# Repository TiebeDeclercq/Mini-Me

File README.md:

# Mini-Me

An animatronic robot that naturally mimics human movements with multiple control interfaces (UDP & Bottango)

## Hardware Overview

The system uses a dual-microcontroller architecture:
- **STM32G030C8T:** Hardware control and servo management
- **ESP32-WROOM-32E-N8:** WiFi communication and external interfaces
- **19 servo motors** controlled via 2x PCA9685 PWM drivers
- **Custom PCBs** for main control and servo distribution
- **12V power supply** with buck converter and current monitoring

## Assembly Instructions

**3D Printed Parts**
The mechanical design consists of 22 different parts, all designed in Fusion 360 for the Bambu Lab P1S printer. Print all STL files from the `/Printfiles/` directory.

**Magnet Integration**
During printing, pause the G-code at specified layers to insert magnets into the head, arms, and legs. This allows easy attachment of accessories and face variations.

**PCB Assembly**
1. Order PCBs using Gerber files in `/Pcb's/`
2. Solder components according to the provided BOMs
3. Main board includes ESP32, STM32, power management, and interfaces
4. Servo boards use JST connectors for secure servo connections

**Final Assembly**
1. Install PCBs in the base/foot assembly
2. Connect servo boards via ribbon cables

3. Mount OLED display and rotary encoder in base

4. Assemble skeleton parts with integrated magnets
5. Connect all servos to appropriate servo board positions

## Software

**Firmware**
- **ESP32:** Programmed with PlatformIO (C++)
- **STM32:** Programmed with STM32CubeIDE

**Control Applications**
- **Mobile App (Flutter):** Smartphone-based control interface via UDP
- **Bottango Integration:** Professional animation software compatibility

**Network Control**
The robot accepts UDP commands in JSON format:
```json
{"servo": 1, "angle": 90}
{"servos": [{"id": 1, "angle": 90}, {"id": 2, "angle": 45}]}
```

## Getting Started

1. **3D Print** all parts from `/Printfiles/`
2. **Order and assemble** PCBs using provided files and BOMs
3. **Flash firmware** from `/Firmware/Mini-Me-DevBoard/` and `/Firmware/MINI-ME-ESP32/`
4. **Install control software** of choice from `/Software/`
5. **Connect to WiFi** and start controlling via UDP or applications

**Project Report:** [Complete documentation available](docs/Mini-Me-Report.pdf)

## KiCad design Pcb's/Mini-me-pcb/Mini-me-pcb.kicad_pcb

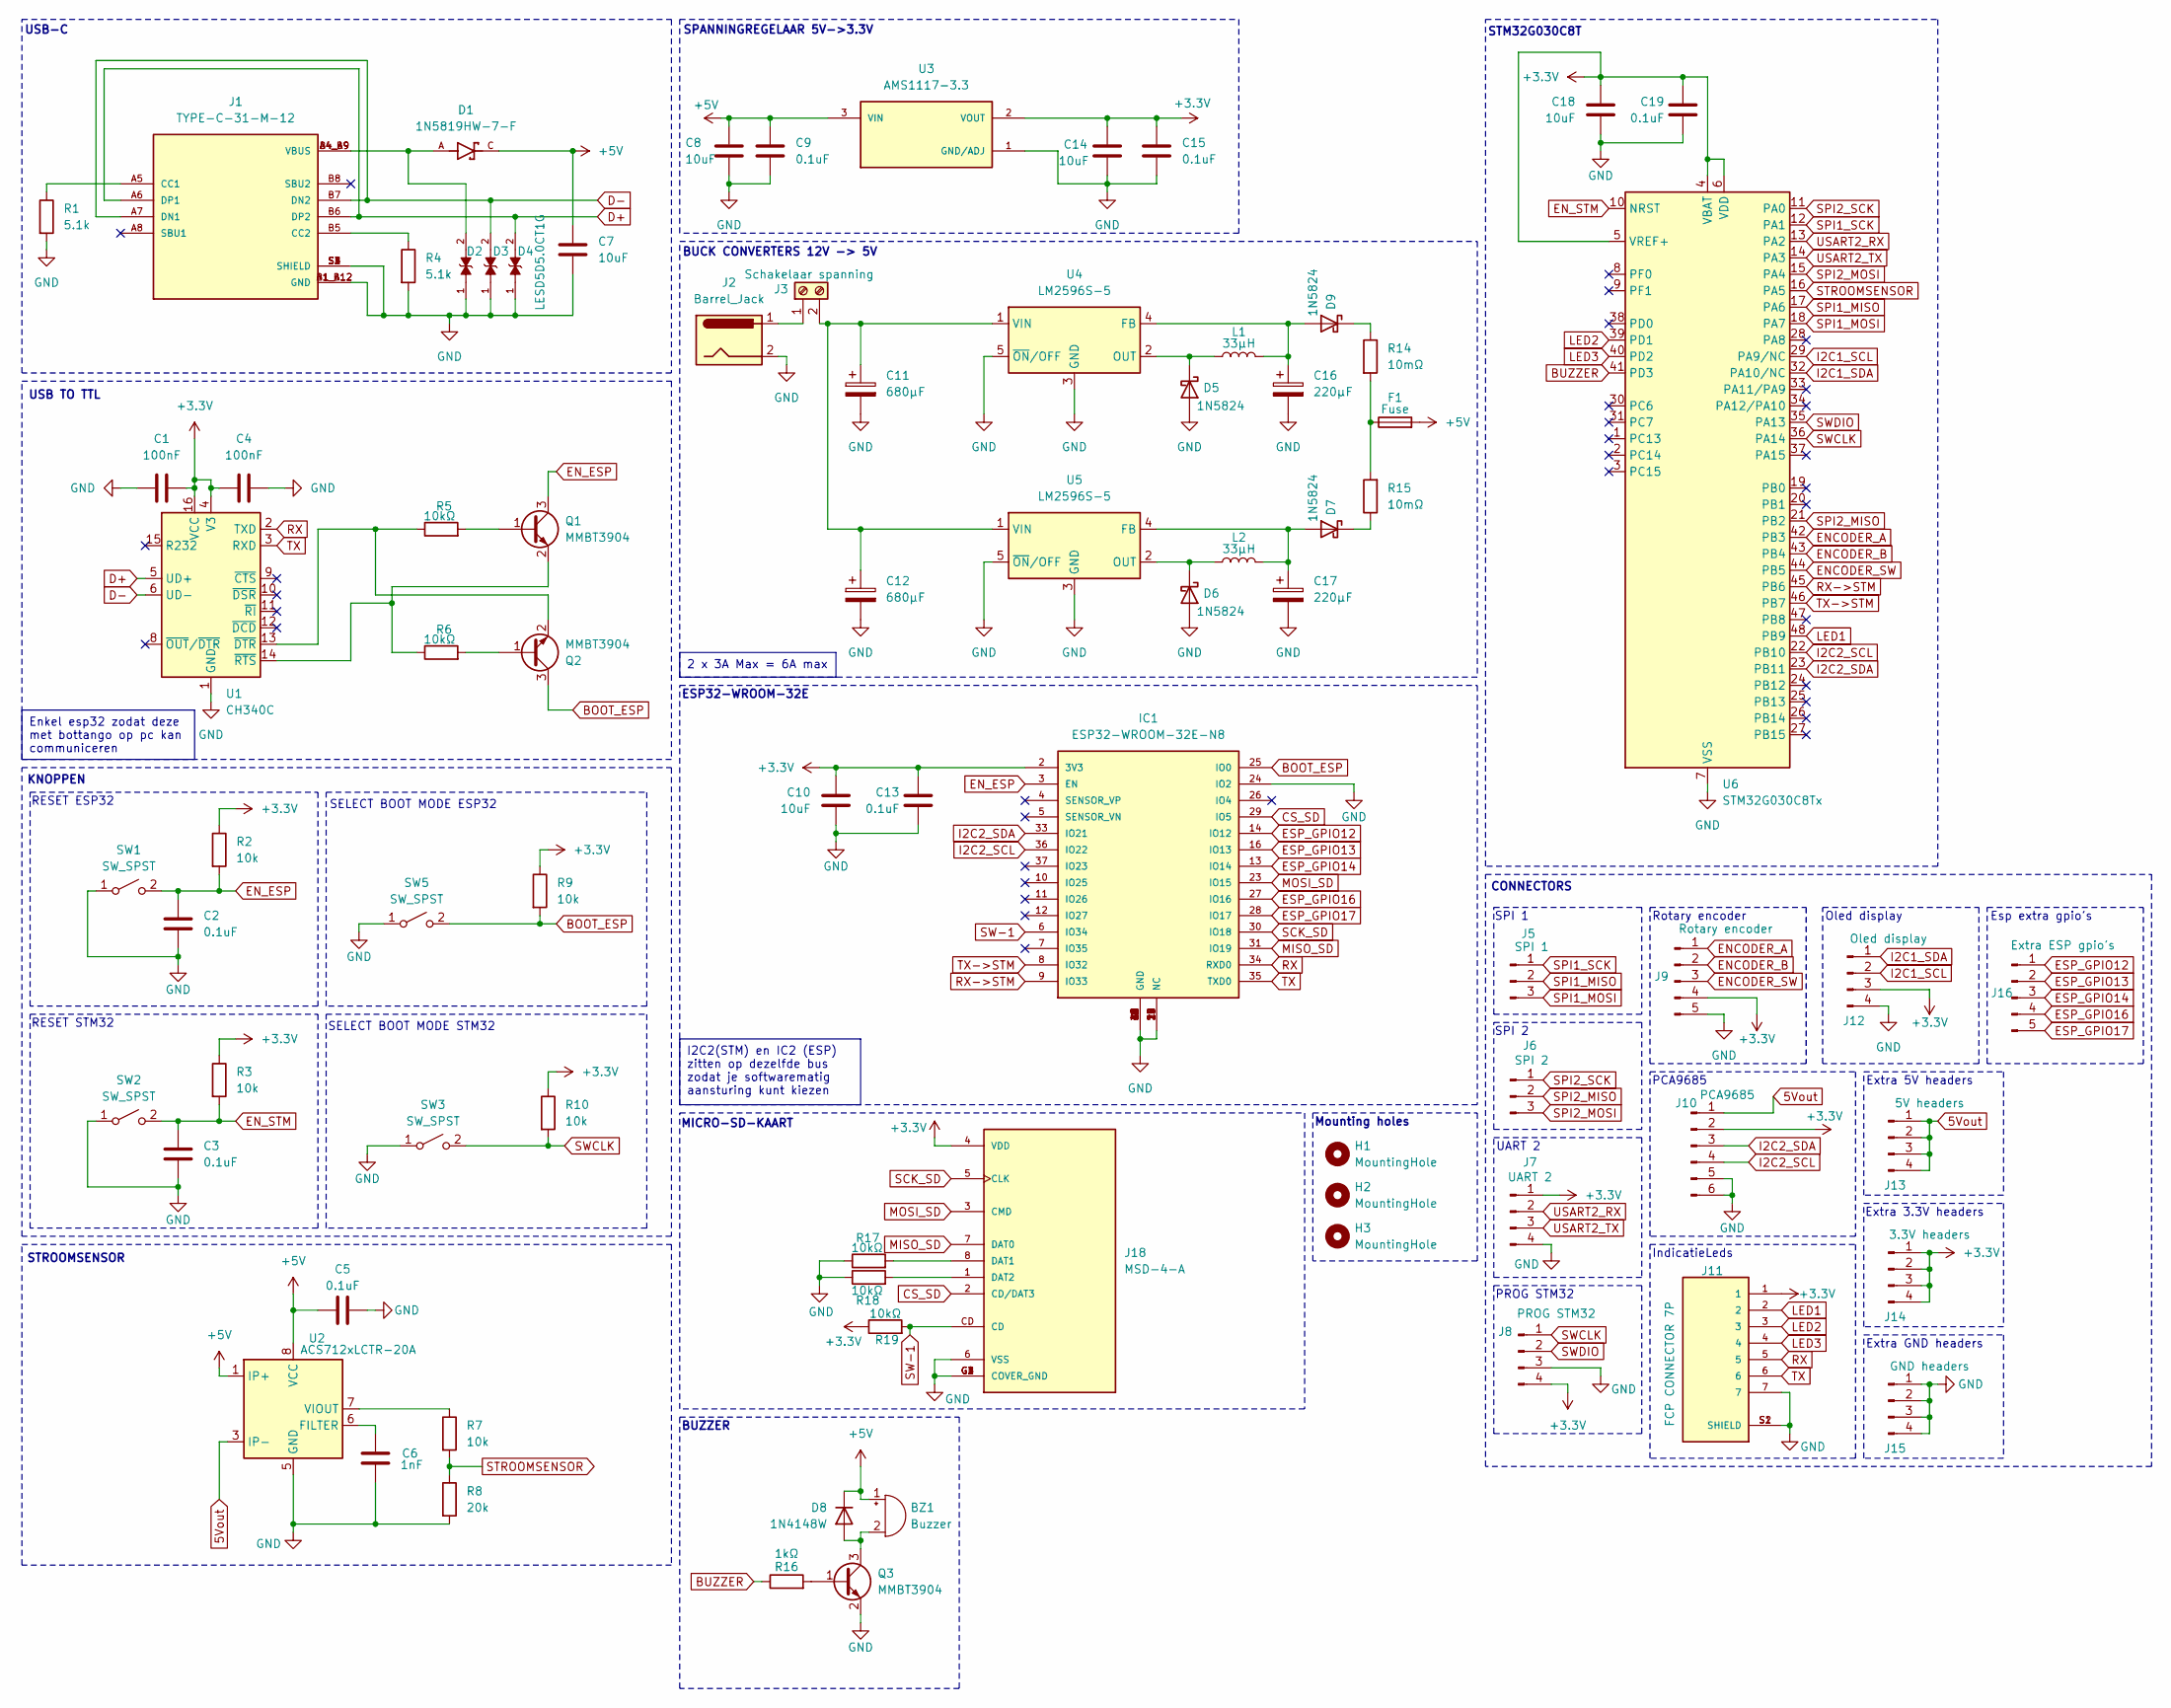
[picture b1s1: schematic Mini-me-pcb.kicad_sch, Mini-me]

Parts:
BZ1: Buzzer; MagneticBuzzer_PUI_AT-0927-TT-6-R
C1, C4: 100nF; C_0805_2012Metric_Pad1.18x1.45mm_HandSolder
C2, C3, C5, C9, C13, C15, C19: 0.1uF; C_0805_2012Metric_Pad1.18x1.45mm_HandSolder
C6: 1nF; C_0805_2012Metric_Pad1.18x1.45mm_HandSolder
C7, C8, C10, C14, C18: 10uF; C_0805_2012Metric_Pad1.18x1.45mm_HandSolder
C11, C12: 680µF; CP_Elec_10x10
C16, C17: 220µF; CP_Elec_6.3x7.7
D1: 1N5819HW-7-F; SOD3715X145N; PARTREV 18-2
D2, D3, D4: LESD5D5.0CT1G; TVS_LESD5D5.0CT1G; PARTREV O
D5, D6, D7, D9: 1N5824; D_SMA
D8: 1N4148W; D_SOD-123
F1: Fuse; Fuse_1206_3216Metric
H1, H2, H3: MountingHole; MountingHole_3.2mm_M3
IC1: ESP32-WROOM-32E-N8; ESP32WROOM32EN8; MOUSER_PART_NUMBER 356-ESP32WRM32E164PH
J1: TYPE-C-31-M-12; HRO_TYPE-C-31-M-12; PARTREV 2020.12.08
J2: Barrel_Jack; BarrelJack_GCT_DCJ200-10-A_Horizontal
J3: Schakelaar spanning; TerminalBlock_Phoenix_MKDS-1,5-2-5.08_1x02_P5.08mm_Horizont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
J5: SPI 1; PinHeader_1x03_P2.54mm_Vertical
J6: SPI 2; PinHeader_1x03_P2.54mm_Vertical
J7: UART 2; PinHeader_1x04_P2.54mm_Vertical
J8: PROG STM32; PinHeader_1x04_P2.54mm_Vertical
J9: Rotary encoder; JST_PH_B5B-PH-K_1x05_P2.00mm_Vertical
J10: PCA9685; JST_PH_B6B-PH-K_1x06_P2.00mm_Vertical
J11: FCP CONNECTOR 7P; FCP7P; PARTREV A4
J12: Oled display; JST_PH_B4B-PH-K_1x04_P2.00mm_Vertical
J13: 5V headers; PinHeader_1x04_P2.54mm_Vertical
J14: 3.3V headers; PinHeader_1x04_P2.54mm_Vertical
J15: GND headers; PinHeader_1x04_P2.54mm_Vertical
J16: Extra ESP gpio's; PinHeader_1x05_P2.54mm_Vertical
J18: MSD-4-A; CUI_MSD-4-A; PARTREV 1.0
L1, L2: 33µH; L_SXN_SMDRI125
Q1, Q2, Q3: MMBT3904; SOT-23
R1, R4: 5.1k; R_0805_2012Metric_Pad1.20x1.40mm_HandSolder
R2, R3, R7, R9, R10: 10k; R_0805_2012Metric_Pad1.20x1.40mm_HandSolder
R5, R6, R17, R18, R19: 10kΩ; R_0805_2012Metric_Pad1.20x1.40mm_HandSolder
R8: 20k; R_0805_2012Metric_Pad1.20x1.40mm_HandSolder
R14, R15: 10mΩ; R_2512_6332Metric
R16: 1kΩ; R_0805_2012Metric_Pad1.20x1.40mm_HandSolder
SW1, SW2, SW3, SW5: SW_SPST; SW_SPST_PTS645
U1: CH340C; SOIC-16_3.9x9.9mm_P1.27mm
U2: ACS712xLCTR-20A; SOIC-8_3.9x4.9mm_P1.27mm
U3: AMS1117-3.3; SOT-223; PARTREV N/A
U4, U5: LM2596S-5; TO-263-5_TabPin3
U6: STM32G030C8Tx; LQFP-48_7x7mm_P0.5mm

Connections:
5Vout: J10.1, J13.1, J13.2, J13.3, J13.4, U2.3 (IP-), U2.4 (IP-)
+3.3V: C1.2, C4.1, C10.1, C13.1, C14.1, C15.1, C18.1, C19.1, IC1.2 (3V3), J7.1, J8.4, J9.4, J10.2, J11.1, J12.3, J14.1, J14.2, J14.3, J14.4, J18.4 (VDD), R2.1, R3.1, R9.1, R10.1, R19.1, U1.4 (V3), U1.16 (VCC), U3.2 (VOUT), U6.4 (VBAT), U6.5 (VREF+), U6.6 (VDD)
+5V: BZ1.1 (-), C5.1, C7.1, C8.1, C9.1, D1.C, D8.1 (K), F1.2, U2.1 (IP+), U2.2 (IP+), U2.8 (VCC), U3.3 (VIN)
BOOT_ESP: IC1.25 (IO0), Q2.3 (C), R9.2, SW5.2 (B)
BUZZER: R16.1, U6.41 (PD3)
CS_SD: IC1.29 (IO5), J18.2 (CD/DAT3)
D+: D4.2, J1.A6 (DP1), J1.B6 (DP2), U1.5 (UD+)
D-: D3.2, J1.A7 (DN1), J1.B7 (DN2), U1.6 (UD-)
ENCODER_A: J9.1, U6.42 (PB3)
ENCODER_B: J9.2, U6.43 (PB4)
ENCODER_SW: J9.3, U6.44 (PB5)
EN_ESP: C2.1, IC1.3 (EN), Q1.3 (C), R2.2, SW1.2 (B)
EN_STM: C3.1, R3.2, SW2.2 (B), U6.10 (NRST)
ESP_GPIO12: IC1.14 (IO12), J16.1
ESP_GPIO13: IC1.16 (IO13), J16.2
ESP_GPIO14: IC1.13 (IO14), J16.3
ESP_GPIO16: IC1.27 (IO16), J16.4
ESP_GPIO17: IC1.28 (IO17), J16.5
GND: C1.1, C2.2, C3.2, C4.2, C5.2, C6.2, C7.2, C8.2, C9.2, C10.2, C11.2, C12.2, C13.2, C14.2, C15.2, C16.2, C17.2, C18.2, C19.2, D2.1, D3.1, D4.1, D5.2 (A), D6.2 (A), IC1.1 (GND), IC1.15 (GND), IC1.17 (NC), IC1.18 (NC), IC1.19 (NC), IC1.20 (NC), IC1.21 (NC), IC1.22 (NC), IC1.24 (IO2), IC1.32 (NC), IC1.38 (GND), IC1.39 (GND), IC1.40 (GND), IC1.41 (GND), IC1.42 (GND), IC1.43 (GND), IC1.44 (GND), IC1.45 (GND), IC1.46 (GND), IC1.47 (GND), J1.A1_B12 (GND), J1.B1_A12 (GND), J1.S1 (SHIELD), J1.S2 (SHIELD), J1.S3 (SHIELD), J1.S4 (SHIELD), J2.2, J7.4, J8.3, J9.5, J10.5, J10.6, J11.7, J11.S1 (SHIELD), J11.S2 (SHIELD), J12.4, J15.1, J15.2, J15.3, J15.4, J18.6 (VSS), J18.G1 (COVER_GND), J18.G2 (COVER_GND), J18.G3 (COVER_GND), J18.G4 (COVER_GND), Q3.2 (E), R1.2, R4.2, R8.2, R17.1, R18.1, SW1.1 (A), SW2.1 (A), SW3.1 (A), SW5.1 (A), U1.1 (GND), U2.5 (GND), U3.1 (GND/ADJ), U4.3 (GND), U4.5 (~ON/OFF), U5.3 (GND), U5.5 (~ON/OFF), U6.7 (VSS)
I2C1_SCL: J12.2, U6.29 (PA9/NC)
I2C1_SDA: J12.1, U6.32 (PA10/NC)
I2C2_SCL: IC1.36 (IO22), J10.4, U6.22 (PB10)
I2C2_SDA: IC1.33 (IO21), J10.3, U6.23 (PB11)
LED1: J11.2, U6.48 (PB9)
LED2: J11.3, U6.39 (PD1)
LED3: J11.4, U6.40 (PD2)
MISO_SD: IC1.31 (IO19), J18.7 (DAT0)
MOSI_SD: IC1.23 (IO15), J18.3 (CMD)
unnamed: BZ1.2 (+), D8.2 (A), Q3.3 (C)
unnamed: D1.A, D2.2, J1.A4_B9 (VBUS), J1.B4_A9 (VBUS)
unnamed: D5.1 (K), L1.1, U4.2 (OUT)
unnamed: D6.1 (K), L2.1, U5.2 (OUT)
unnamed: C17.1, D7.2 (A), L2.2, U5.4 (FB)
unnamed: D7.1 (K), R15.1
unnamed: C16.1, D9.2 (A), L1.2, U4.4 (FB)
unnamed: D9.1 (K), R14.1
unnamed: F1.1, R14.2, R15.2
unnamed: J1.A5 (CC1), R1.1
unnamed: J1.B5 (CC2), R4.1
unnamed: J2.1, J3.1
unnamed: C11.1, C12.1, J3.2, U4.1 (VIN), U5.1 (VIN)
unnamed: J18.8 (DAT1), R17.2
unnamed: J18.1 (DAT2), R18.2
unnamed: Q1.1 (B), R5.2
unnamed: Q1.2 (E), R6.1, U1.14 (~RTS)
unnamed: Q2.1 (B), R6.2
unnamed: Q2.2 (E), R5.1, U1.13 (~DTR)
unnamed: Q3.1 (B), R16.2
unnamed: C6.1, U2.6 (FILTER)
unnamed: R7.1, U2.7 (VIOUT)
RX: IC1.34 (RXD0), J11.5, U1.2 (TXD)
RX->STM: IC1.9 (IO33), U6.45 (PB6)
SCK_SD: IC1.30 (IO18), J18.5 (CLK)
SPI1_MISO: J5.2, U6.17 (PA6)
SPI1_MOSI: J5.3, U6.18 (PA7)
SPI1_SCK: J5.1, U6.12 (PA1)
SPI2_MISO: J6.2, U6.21 (PB2)
SPI2_MOSI: J6.3, U6.15 (PA4)
SPI2_SCK: J6.1, U6.11 (PA0)
STROOMSENSOR: R7.2, R8.1, U6.16 (PA5)
SW-1: IC1.6 (IO34), J18.CD, R19.2
SWCLK: J8.1, R10.2, SW3.2 (B), U6.36 (PA14)
SWDIO: J8.2, U6.35 (PA13)
TX: IC1.35 (TXD0), J11.6, U1.3 (RXD)
TX->STM: IC1.8 (IO32), U6.46 (PB7)
USART2_RX: J7.2, U6.13 (PA2)
USART2_TX: J7.3, U6.14 (PA3)

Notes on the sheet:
I2C2(STM) en IC2 (ESP) zitten op dezelfde bus zodat je softwarematig aansturing kunt kiezen
Enkel esp32 zodat deze met bottango op pc kan communiceren
2 x 3A Max = 6A max
STM32G030C8T
SELECT BOOT MODE ESP32
SPI 2
BUZZER
Extra 3.3V headers
Oled display
Mounting holes
STROOMSENSOR
Extra GND headers
MICRO-SD-KAART
USB-C
Esp extra gpio's
SPANNINGREGELAAR 5V->3.3V
Rotary encoder
IndicatieLeds
UART 2
Extra 5V headers
SELECT BOOT MODE STM32
KNOPPEN
SPI 1
PCA9685
RESET STM32
RESET ESP32
CONNECTORS
USB TO TTL
BUCK CONVERTERS 12V -> 5V
ESP32-WROOM-32E
PROG STM32

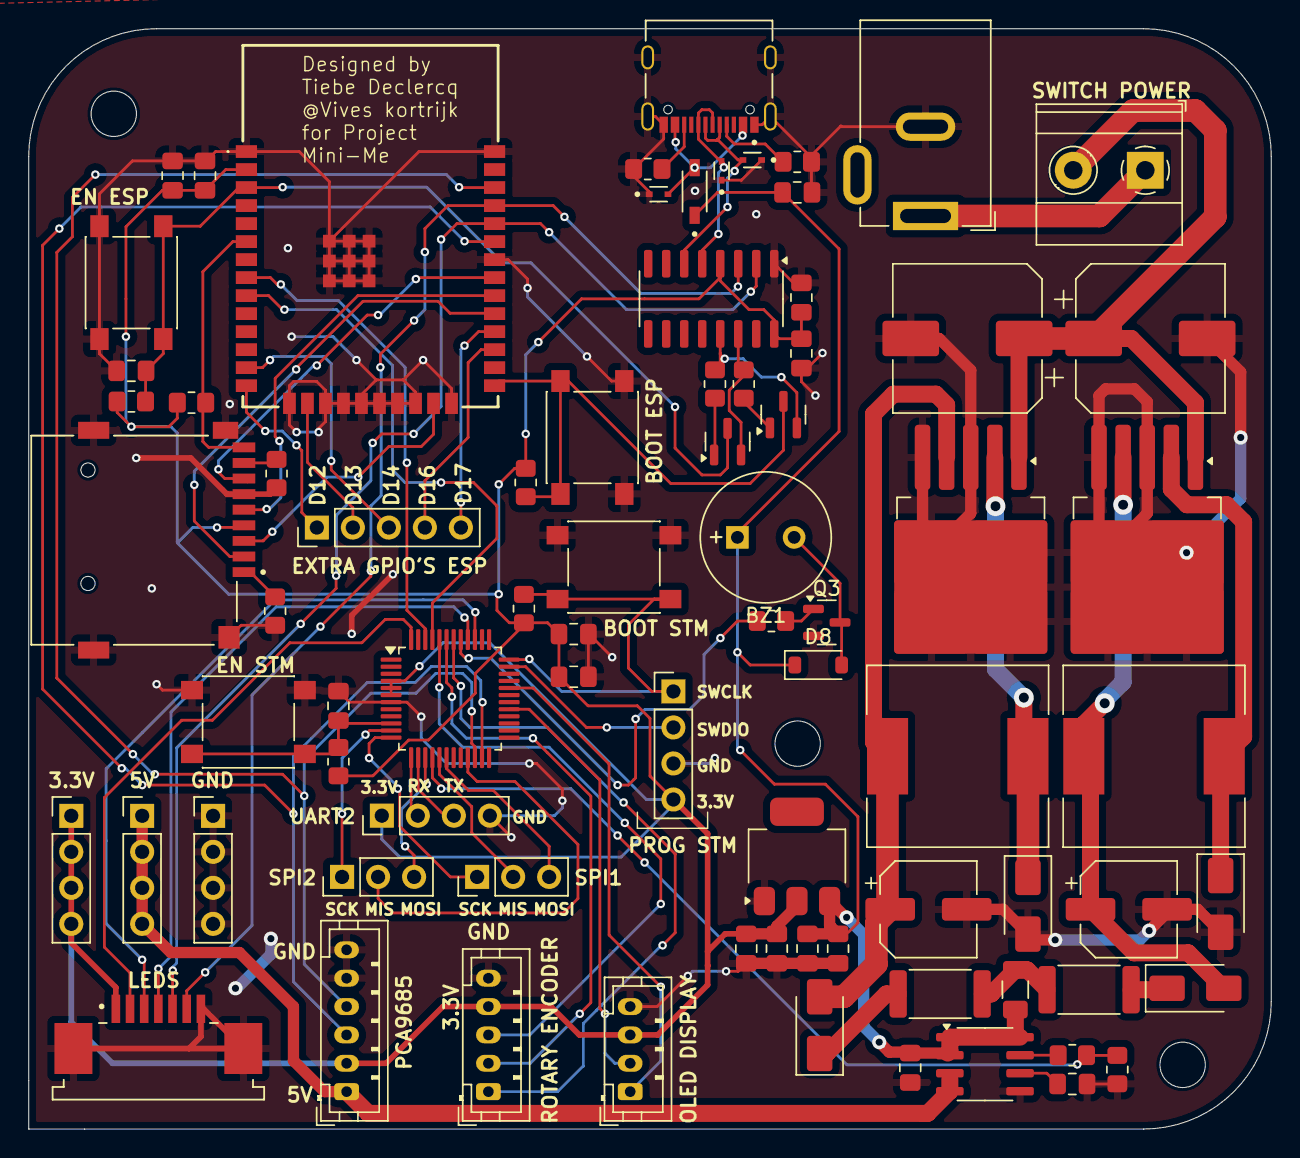
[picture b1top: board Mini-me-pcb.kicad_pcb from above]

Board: 2 copper layers, 87.6 x 77.6 mm, 81 parts (0 on the bottom side), 67 nets.

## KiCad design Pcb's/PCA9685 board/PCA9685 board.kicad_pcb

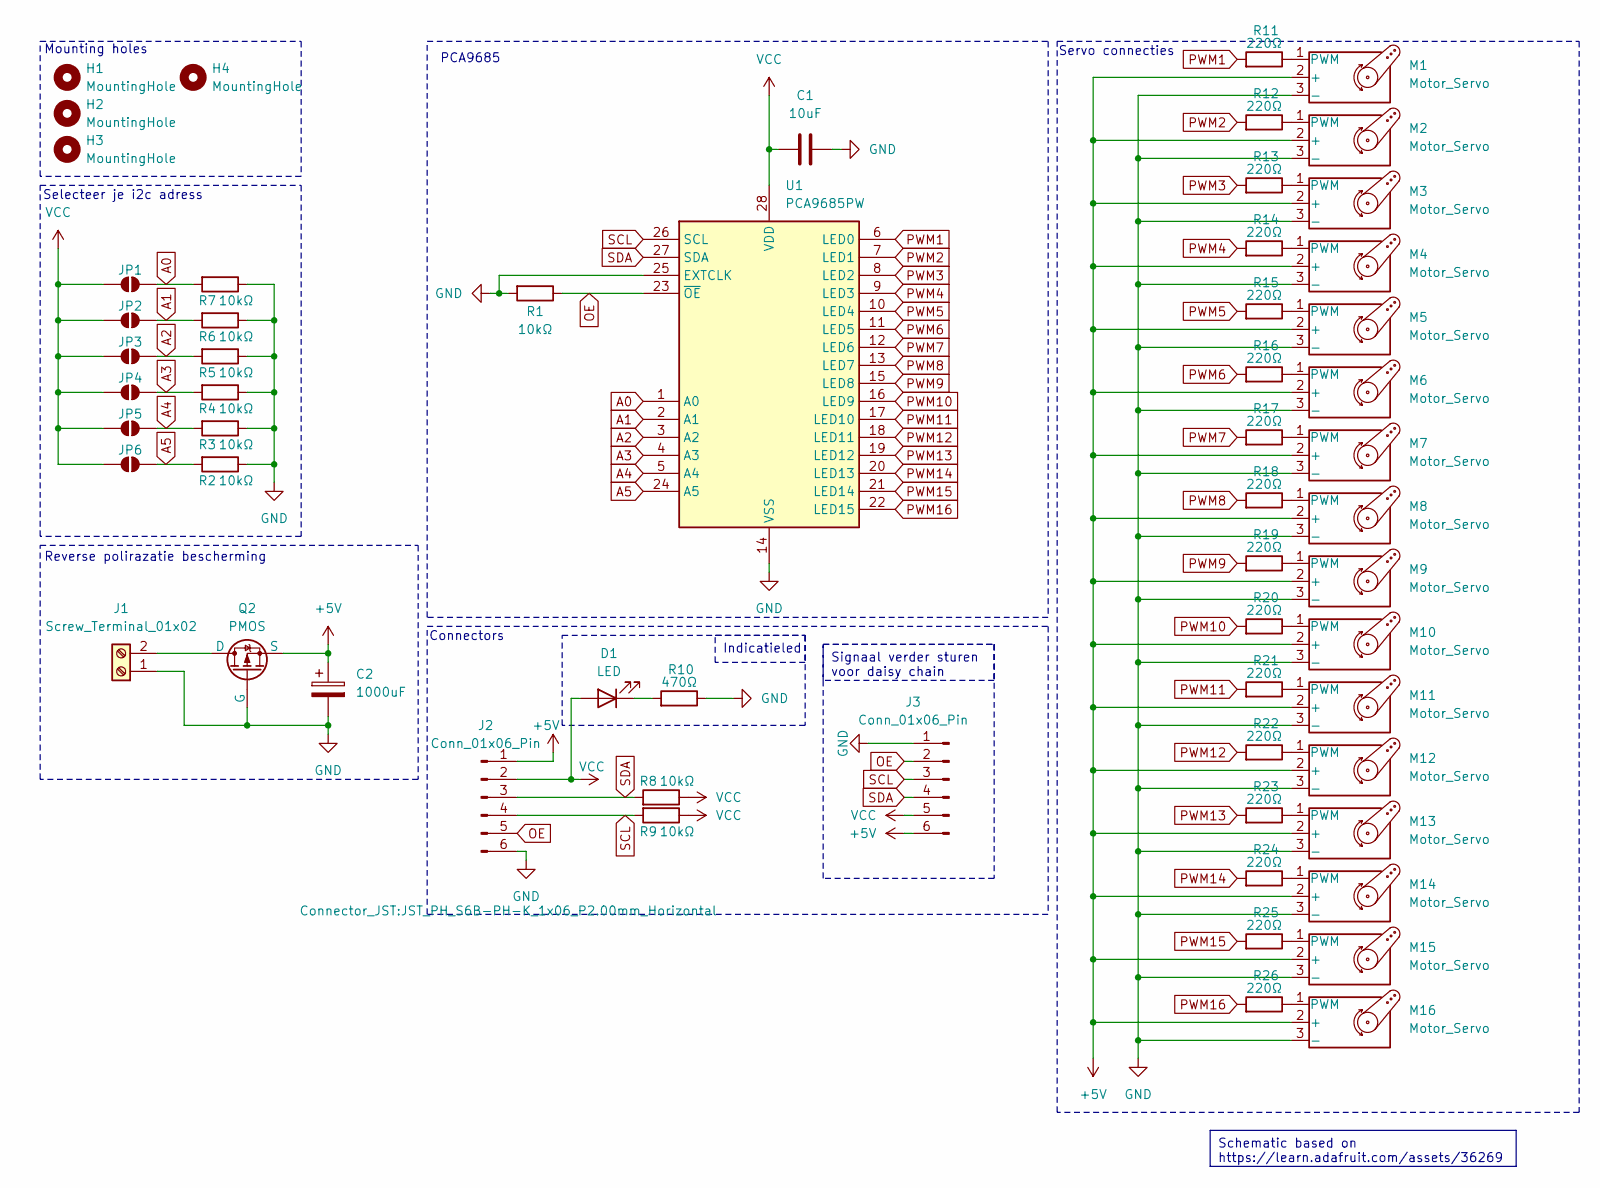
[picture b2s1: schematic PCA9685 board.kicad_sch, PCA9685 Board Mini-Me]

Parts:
C1: 10uF; C_0805_2012Metric_Pad1.18x1.45mm_HandSolder
C2: 1000uF; CP_Elec_8x10.5
D1: LED; LED_0805_2012Metric_Pad1.15x1.40mm_HandSolder
H1, H2, H3, H4: MountingHole; MountingHole_3.2mm_M3
J1: Screw_Terminal_01x02; TerminalBlock_Phoenix_MKDS-1,5-2-5.08_1x02_P5.08mm_Horizont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
J2, J3: Conn_01x06_Pin; JST_PH_S6B-PH-K_1x06_P2.00mm_Horizontal
JP1, JP2, JP3, JP4, JP5, JP6: SolderJumper_2_Open; SolderJumper-2_P1.3mm_Open_RoundedPad1.0x1.5mm
M1, M2, M3, M4, M5, M6, M7, M8, M9, M10, M11, M12, M13, M14, M15, M16: Motor_Servo; PinHeader_1x03_P2.54mm_Vertical
Q2: PMOS; SOT-23
R1, R2, R3, R4, R5, R6, R7, R8, R9: 10kΩ; R_0805_2012Metric_Pad1.20x1.40mm_HandSolder
R10: 470Ω; R_0805_2012Metric_Pad1.20x1.40mm_HandSolder
R11, R12, R13, R14, R15, R16, R17, R18, R19, R20, R21, R22, R23, R24, R25, R26: 220Ω; R_0805_2012Metric_Pad1.20x1.40mm_HandSolder
U1: PCA9685PW; TSSOP-28_4.4x9.7mm_P0.65mm

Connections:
+5V: C2.1, J2.1, J3.6, M1.2 (+), M2.2 (+), M3.2 (+), M4.2 (+), M5.2 (+), M6.2 (+), M7.2 (+), M8.2 (+), M9.2 (+), M10.2 (+), M11.2 (+), M12.2 (+), M13.2 (+), M14.2 (+), M15.2 (+), M16.2 (+), Q2.3 (S)
A0: JP1.2 (B), R7.2, U1.1 (A0)
A1: JP2.2 (B), R6.2, U1.2 (A1)
A2: JP3.2 (B), R5.2, U1.3 (A2)
A3: JP4.2 (B), R4.2, U1.4 (A3)
A4: JP5.2 (B), R3.2, U1.5 (A4)
A5: JP6.2 (B), R2.2, U1.24 (A5)
GND: C1.2, C2.2, J1.1, J2.6, J3.1, M1.3 (-), M2.3 (-), M3.3 (-), M4.3 (-), M5.3 (-), M6.3 (-), M7.3 (-), M8.3 (-), M9.3 (-), M10.3 (-), M11.3 (-), M12.3 (-), M13.3 (-), M14.3 (-), M15.3 (-), M16.3 (-), Q2.2 (G), R1.2, R2.1, R3.1, R4.1, R5.1, R6.1, R7.1, R10.1, U1.14 (VSS), U1.25 (EXTCLK)
unnamed: D1.1 (K), R10.2
unnamed: J1.2, Q2.1 (D)
unnamed: M1.1 (PWM), R11.1
unnamed: M2.1 (PWM), R12.1
unnamed: M3.1 (PWM), R13.1
unnamed: M4.1 (PWM), R14.1
unnamed: M5.1 (PWM), R15.1
unnamed: M6.1 (PWM), R16.1
unnamed: M7.1 (PWM), R17.1
unnamed: M8.1 (PWM), R18.1
unnamed: M9.1 (PWM), R19.1
unnamed: M10.1 (PWM), R20.1
unnamed: M11.1 (PWM), R21.1
unnamed: M12.1 (PWM), R22.1
unnamed: M13.1 (PWM), R23.1
unnamed: M14.1 (PWM), R24.1
unnamed: M15.1 (PWM), R25.1
unnamed: M16.1 (PWM), R26.1
OE: J2.5, J3.2, R1.1, U1.23 (~OE)
PWM1: R11.2, U1.6 (LED0)
PWM2: R12.2, U1.7 (LED1)
PWM3: R13.2, U1.8 (LED2)
PWM4: R14.2, U1.9 (LED3)
PWM5: R15.2, U1.10 (LED4)
PWM6: R16.2, U1.11 (LED5)
PWM7: R17.2, U1.12 (LED6)
PWM8: R18.2, U1.13 (LED7)
PWM9: R19.2, U1.15 (LED8)
PWM10: R20.2, U1.16 (LED9)
PWM11: R21.2, U1.17 (LED10)
PWM12: R22.2, U1.18 (LED11)
PWM13: R23.2, U1.19 (LED12)
PWM14: R24.2, U1.20 (LED13)
PWM15: R25.2, U1.21 (LED14)
PWM16: R26.2, U1.22 (LED15)
SCL: J2.4, J3.3, R9.2, U1.26 (SCL)
SDA: J2.3, J3.4, R8.2, U1.27 (SDA)
VCC: C1.1, D1.2 (A), J2.2, J3.5, JP1.1 (A), JP2.1 (A), JP3.1 (A), JP4.1 (A), JP5.1 (A), JP6.1 (A), R8.1, R9.1, U1.28 (VDD)

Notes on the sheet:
Schematic based on https://learn.adafruit.com/assets/36269
Indicatieled
Signaal verder sturen voor daisy chain
Mounting holes
Connectors
PCA9685
Reverse polirazatie bescherming
Selecteer je i2c adress
Servo connecties

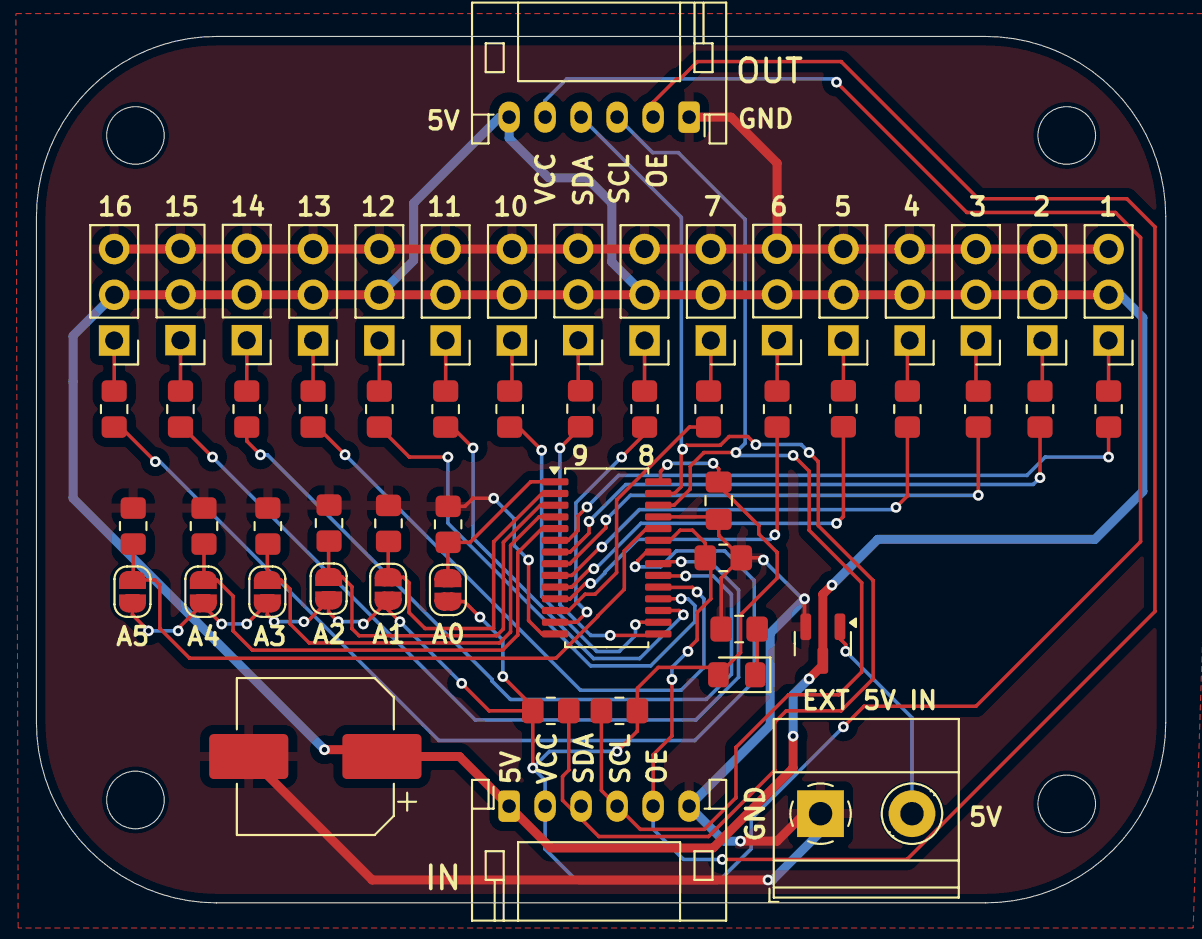
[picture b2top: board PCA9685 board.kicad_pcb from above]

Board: 2 copper layers, 62.7 x 48.1 mm, 60 parts (0 on the bottom side), 46 nets.

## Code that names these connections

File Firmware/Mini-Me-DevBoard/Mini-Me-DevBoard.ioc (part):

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Mcu.Name=STM32G030C(6-8)Tx
Mcu.Package=LQFP48
Mcu.UserName=STM32G030C8Tx
PA0.Signal=GPIO_Output
PA10.Mode=I2C
PA10.Signal=I2C1_SDA
PA2.Mode=Asynchronous
PA2.Signal=USART2_TX
PA3.Mode=Asynchronous
PA3.Signal=USART2_RX
PA5.Signal=GPIO_Analog
PA9.Mode=I2C
PA9.Signal=I2C1_SCL
PB10.Signal=GPIO_Input
PB11.Signal=GPIO_Input
PB3.Signal=GPIO_Input
PB4.Signal=GPIO_Input
PB5.Signal=GPIO_Input
PB6.Mode=Asynchronous
PB6.Signal=USART1_TX
PB7.Mode=Asynchronous
PB7.Signal=USART1_RX
PB9.Signal=GPIO_Output
PD1.Signal=GPIO_Output
PD2.Signal=GPIO_Output
PD3.Signal=GPIO_Output
RCC.HSE_VALUE=8000000
RCC.SYSCLKFreq_VALUE=16000000
board=custom

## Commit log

2025-05-31 INIT

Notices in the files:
Pcb's/PCA9685 board/PCA9685 board.kicad_pcb:
©Dectronics
